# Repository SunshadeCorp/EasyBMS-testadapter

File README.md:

# EasyBMS Testadapter
PCB of the EasyBMS testadapter for end of line test as an EAGLE project

Used design rules from [here](https://github.com/JLCPCB/jlcpcb-eagle) with one modification: under "Masks" in DRC settings, set "Limit" to 20mil to cover vias that have smaller drill size with solder mask.

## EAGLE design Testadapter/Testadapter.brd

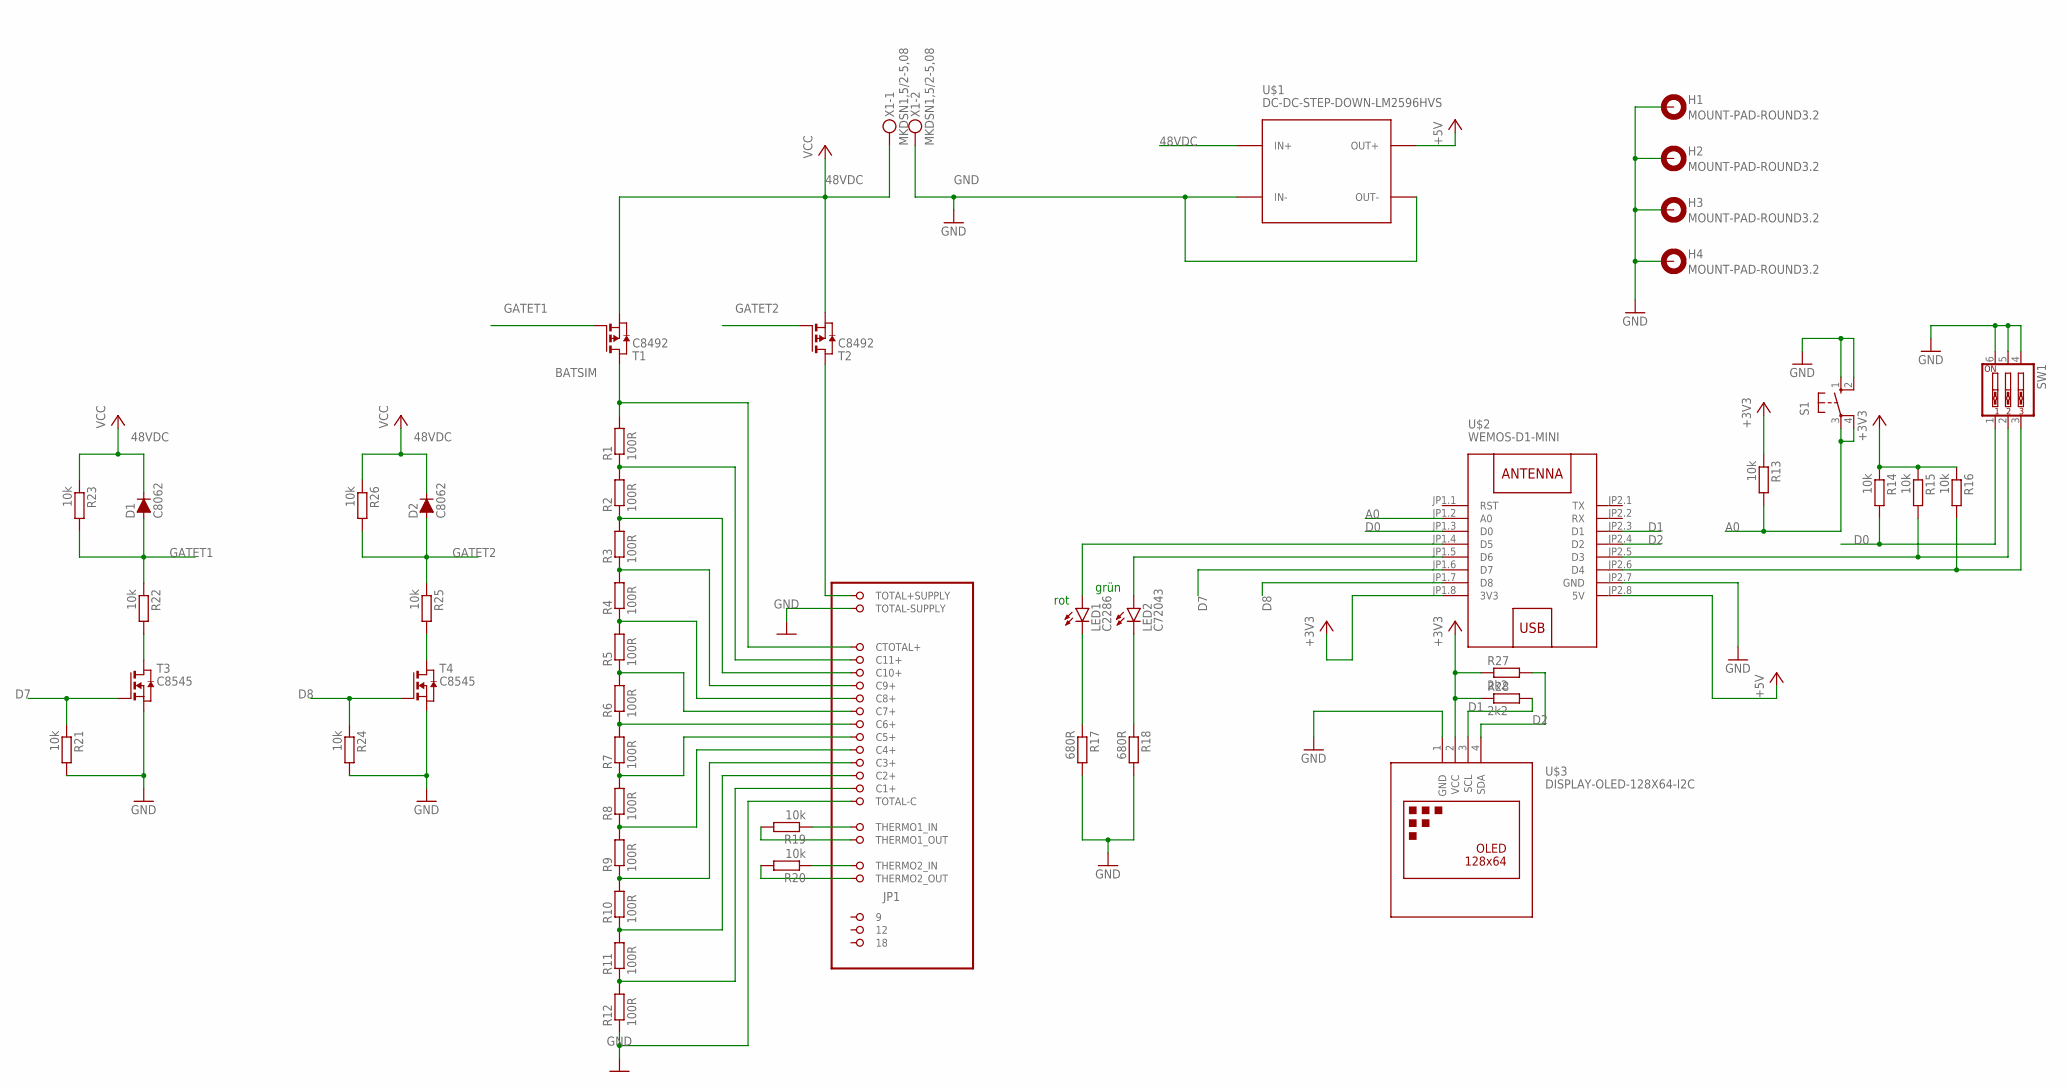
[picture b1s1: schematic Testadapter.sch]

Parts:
D1, D2: C8062; MELF-MLL34
H1, H2, H3, H4: MOUNT-PAD-ROUND3.2; 3,2-PAD
JP1: PINHD-2X11_MEB12S_MODULSEITE_SMD; 2X11_MEB12S_MODULSEITE_SMD
LED1: C2286; CHIP-LED0603
LED2: C72043; CHIP-LED0603
R1, R2, R3, R4, R5, R6, R7, R8, R9, R10, R11, R12: 100R; R0805
R13, R14, R15, R16, R19, R20, R21, R22, R23, R24, R25, R26: 10k; R0805
R17, R18: 680R; R0805
R27, R28: 2k2; R0805
S1: 10-XX; B3F-10XX
SW1: SW_DIP-3; EDG-03
T1, T2: C8492; SOT-23
T3, T4: C8545; SOT-23
U$1: DC-DC-STEP-DOWN-LM2596HVS
U$2: WEMOS-D1-MINI
U$3: DISPLAY-OLED-128X64-I2C
X1: MKDSN1,5/2-5,08

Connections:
48VDC: D1.1 (C), D2.1 (C), R23.1, R26.1, T1.2 (S), T2.2 (S), U$1.IN+, X1.1
+3V3: R13.1, R14.1, R15.1, R16.1, R27.1, R28.1, U$2.JP1.8 (3V3), U$3.2 (VCC)
+5V: U$1.OUT+, U$2.JP2.8 (5V)
A0: R13.2, S1.3, S1.4 (P1), U$2.JP1.2 (A0)
BATSIM: JP1.21 (CTOTAL+), R1.2, T1.1 (D)
D0: R14.2, SW1.1, U$2.JP1.3 (D0)
D1: R28.2, U$2.JP2.3 (D1), U$3.3 (SCL)
D2: R27.2, U$2.JP2.4 (D2), U$3.4 (SDA)
D7: R21.1, T3.3 (G), U$2.JP1.6 (D7)
D8: R24.1, T4.3 (G), U$2.JP1.7 (D8)
GATET1: D1.2 (A), R22.1, R23.2, T1.3 (G)
GATET2: D2.2 (A), R25.1, R26.2, T2.3 (G)
GND: H1.B3,2, H2.B3,2, H3.B3,2, H4.B3,2, JP1.7 (TOTAL-SUPPLY), JP1.9 (TOTAL-C), R12.1, R17.2, R18.2, R21.2, R24.2, S1.1 (S), S1.2 (S1), SW1.4, SW1.5, SW1.6, T3.2 (S), T4.2 (S), U$1.IN-, U$1.OUT-, U$2.JP2.7 (GND), U$3.1 (GND), X1.2
unnamed: JP1.20 (C11+), R1.1, R2.2
unnamed: JP1.19 (C10+), R2.1, R3.2
unnamed: JP1.18 (C9+), R3.1, R4.2
unnamed: JP1.17 (C8+), R4.1, R5.2
unnamed: JP1.16 (C7+), R5.1, R6.2
unnamed: JP1.15 (C6+), R6.1, R7.2
unnamed: JP1.14 (C5+), R7.1, R8.2
unnamed: JP1.13 (C4+), R8.1, R9.2
unnamed: JP1.12 (C3+), R9.1, R10.2
unnamed: JP1.11 (C2+), R10.1, R11.2
unnamed: JP1.10 (C1+), R11.1, R12.2
unnamed: R15.2, SW1.2, U$2.JP2.5 (D3)
unnamed: R16.2, SW1.3, U$2.JP2.6 (D4)
unnamed: LED1.C, R17.1
unnamed: LED2.C, R18.1
unnamed: JP1.22 (TOTAL+SUPPLY), T2.1 (D)
unnamed: LED2.A, U$2.JP1.5 (D6)
unnamed: LED1.A, U$2.JP1.4 (D5)
unnamed: R22.2, T3.1 (D)
unnamed: R25.2, T4.1 (D)
THERMO1IN: JP1.1 (THERMO1_IN), R19.1
THERMO1OUT: JP1.3 (THERMO1_OUT), R19.2
THERMO2_IN: JP1.2 (THERMO2_IN), R20.1
THERMO2_OUT: JP1.4 (THERMO2_OUT), R20.2

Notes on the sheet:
rot
grün

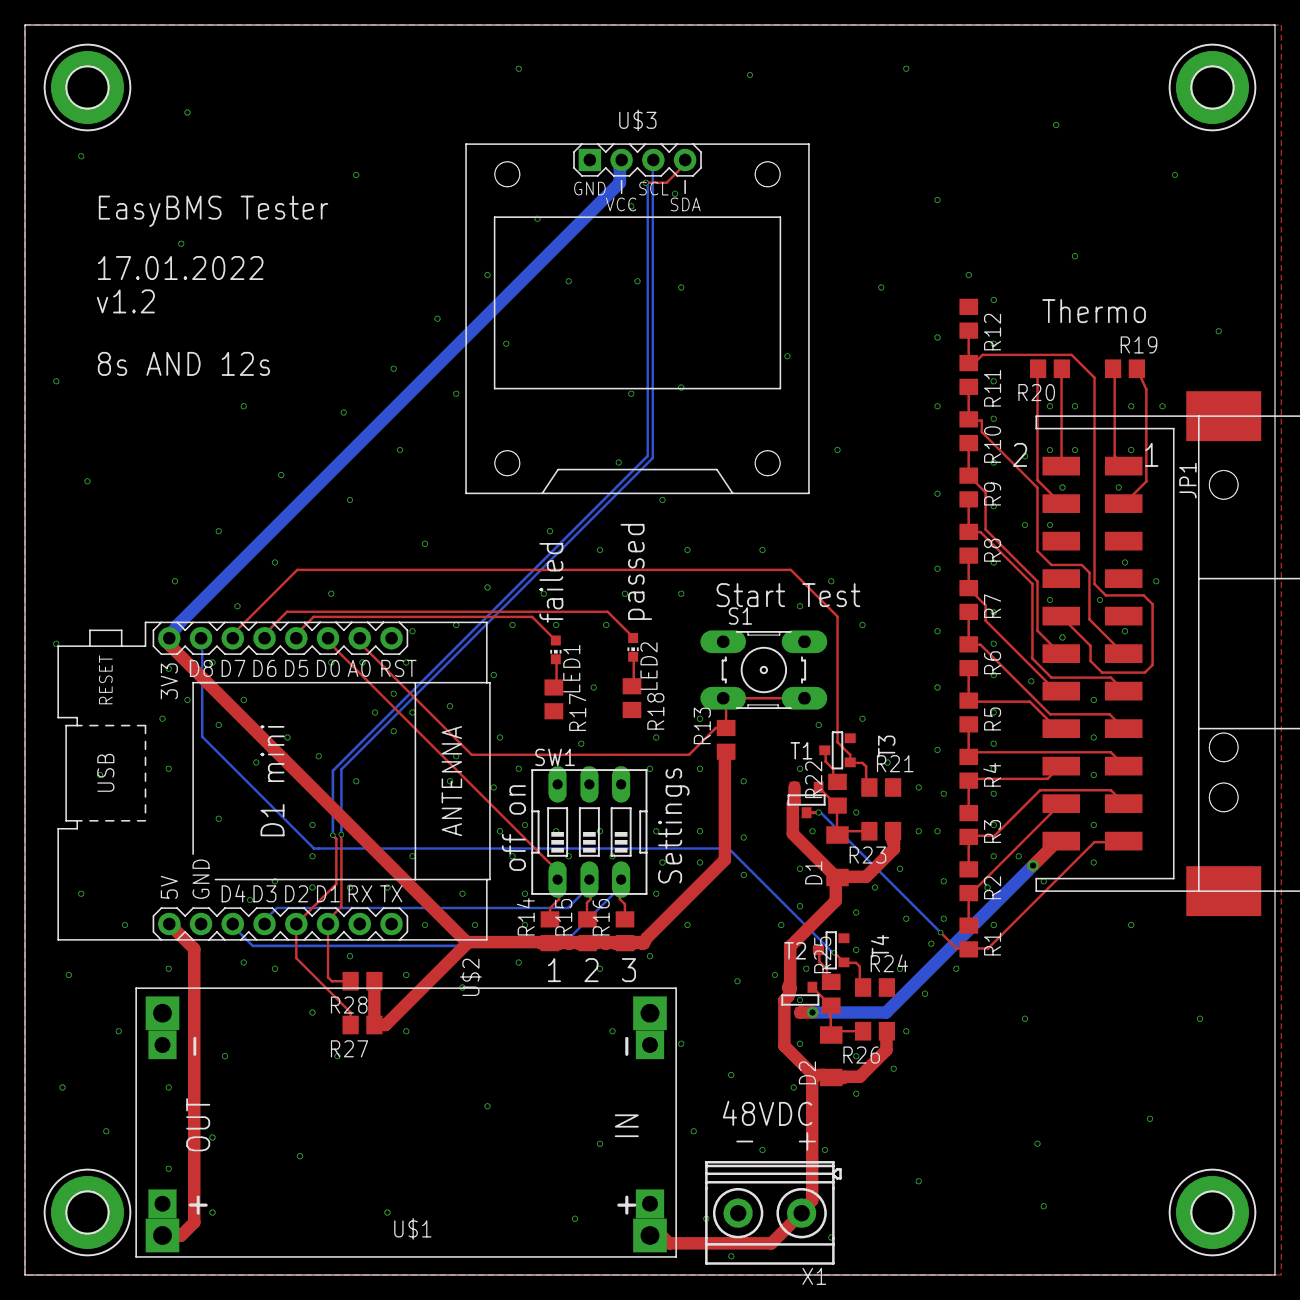
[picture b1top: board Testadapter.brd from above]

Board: 2 copper layers, 100.0 x 100.0 mm, 47 parts (0 on the bottom side), 37 nets.

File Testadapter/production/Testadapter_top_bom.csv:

Comment,Designator,Footprint,LCSC Part #
2k2,R27 R28,R0805,
10k,R13 R14 R15 R16 R19 R20 R21 R22 R23 R24 R25 R26,R0805,
100R,R1 R2 R3 R4 R5 R6 R7 R8 R9 R10 R11 R12,R0805,
680R,R17 R18,R0805,
C2286,LED1,CHIP-LED0603,
C8062,D1 D2,MELF-MLL34,
C8492,T1 T2,SOT-23,
C8545,T3 T4,SOT-23,
C72043,LED2,CHIP-LED0603,

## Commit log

2021-12-03 Initial commit, copied from EasyBMS_Hardware repo
2021-12-12 routing and placement updated, dimensions changed
2021-12-13 display added
2021-12-13 routing updated
2021-12-13 text added
2021-12-13 text added and diodes defined
2021-12-13 gerber files added
2021-12-13 layout slightly change, new revision
2022-01-16 Testscript for Hardwarecheck added
2022-01-16 fixed PFETs reverse orientation, v1.2
2022-01-17 initial platformIO project added
2022-01-17 Adafruit libraries added
2022-01-17 fix of the platformio.ini
2022-01-17 basic stepsequence built
2022-01-17 sample stepsequence running
2022-01-17 pinhead_own library hinzugefügt
2022-01-18 updated library with SMD footprint of BMS connector
2022-01-18 added description on footprints
2022-01-18 new smd footprint of BMS connector integrated
2022-01-22 MQTT broker and client added
2022-02-05 Remove uMQTTBroker as pio library and added the latest version into include folder
2022-02-05 put uMQTTBroker into lib directory
2022-02-05 Added derived mqtt broker class and subscribed bms topics
2022-04-05 deleted testadapter firmware, which was moved to own repo
2022-04-06 apply new folder structure, renamed files, stripped EAGLE lib for MEB connectors
2022-04-06 changed design rules to cover vias with solder mask and updated README accordingly

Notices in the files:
parts and their libraries:
diy-modules: Released under the Creative Commons Attribution 4.0 International License: http://creativecommons.org/licenses/by/4.0
